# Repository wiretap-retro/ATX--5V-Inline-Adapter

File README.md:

# ATX -5V Inline Adapter
A small inline adapter for an ATX power supply to generate -5VDC for Retro PC's connecting via AT P8/P9 connectors. This adapter has been tested and works great.

## Components Needed
* C1 - Kemet T491C225K025AT
* C2 - Kemet T491C105K050AT
* U1 - STMicroelectronics L7905CV
* PCB from the Gerber files in this project (JLCPCB, OSH Park, PCBway, etc.)
* ATX to AT wiring harness adapter (Aliexpress, Amazon, Ebay, etc.)
* Heatshrink tubing

## Installation
* Solder C1 and C2 capacitors.
* Solder U1, making sure to bend the legs at the appropriate length. Clip the excess.
* Use a reference of the ATX and AT power pinouts to find the -12V, -5V and GND connections on the ATX to AT harness. Be careful, because some of the harnesses have incorrect color wires.
* Cut the wires in an appropriate location to solder the -5V adapter in place. Start at the top side (ATX connector side) with -12V and GND wires.
* Strip the -12V and GND wires that are attached to the ATX connector side and solder them to the PCB side with the 2 plated through-holes.
* The -12V, -5V and GND on the AT side needs to be cut back to the length of the PCB and stripped.
* Place your heatshrink over the 3 wires and slide it down.
* Solder the -12V, -5V and GND from the AT side to the PCB with the 3 plated through-holes.
* Place the heatshrink over the PCB and heat it up to shrink it in place. This will protect against short circuits while installed in your computer.
* There should be one -5V wire hanging from the ATX side of your wire harness. Place some small heatshrink over the end of it to insulate it, or just remove it from the ATX side of the harness if you have the pin removal tool available.

This is what it should look like when finished!

## Other
This project is open source hardware. Do what you want with it.

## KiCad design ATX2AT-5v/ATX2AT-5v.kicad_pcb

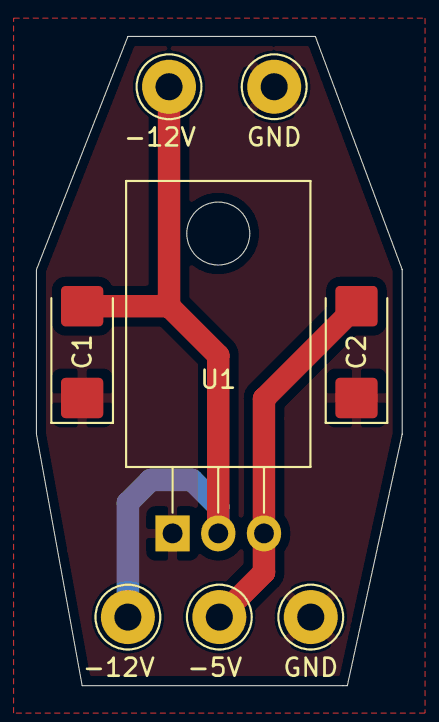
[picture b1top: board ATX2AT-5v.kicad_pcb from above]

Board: 2 copper layers, 20.3 x 36.1 mm, 8 parts (0 on the bottom side), 3 nets.

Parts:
-5V, -12V, -12V#2: Conn_01x01; Pin_D1.3mm_L11.0mm_LooseFit
C1: 2.2uF; CP_EIA-6032-28_Kemet-C_Pad2.25x2.35mm_HandSolder
C2: 1uF; CP_EIA-6032-28_Kemet-C_Pad2.25x2.35mm_HandSolder
GND: Conn_01x01; Pin_D1.3mm_L11.0mm_LooseFit
GND#2: Conn_01x01; Pin_D1.3mm_L11.0mm_LooseFit
U1: LM7905_TO220; TO-220-3_Horizontal_TabDown

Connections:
unnamed: C1.1, C2.1, GND.1, GND#2.1, U1.1
unnamed: -12V.1, -12V#2.1, C1.2, U1.2
unnamed: -5V.1, C2.2, U1.3

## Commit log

2022-09-08 Initial upload
